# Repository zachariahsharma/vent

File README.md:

# Vynte Vent

KiCad hardware design for the Vynte smart vent, a battery-powered register for room-by-room HVAC comfort. The saved project revision is **v0.5.0**.

## Design files

- `Vent.kicad_pro`: open this project in KiCad.
- `Vent.kicad_sch` and `Vent.kicad_pcb`: main schematic and PCB layout.
- `3.3V-Buck-Boost.kicad_sch`, `5V-Boost.kicad_sch`, and `ExternalAutoprogramming.kicad_sch`: supporting schematic sheets.
- `production/`: saved fabrication archive, assembly CSV exports, IPC netlist, and stencil layers.
- `fabrication-toolkit-options.json`: saved fabrication export settings.

## Fabrication status

The production files are existing exports preserved with the project. The fabrication ZIP was generated on September 21, 2026; the PCB source was saved later, on September 22. These exports have not been verified against the latest source. Regenerate and review fabrication files, DRC, and ERC before ordering boards.

Local backups, analysis caches, and per-user KiCad settings are excluded from version control.

## Repository copies

Gitea is the development repository. The public GitHub copy includes the development history with credential files removed from every revision. Commit author and committer identities have been normalized to Zachariah K. Sharma at the repository owner's request; Gitea retains the original history.

No open-source license has been selected.

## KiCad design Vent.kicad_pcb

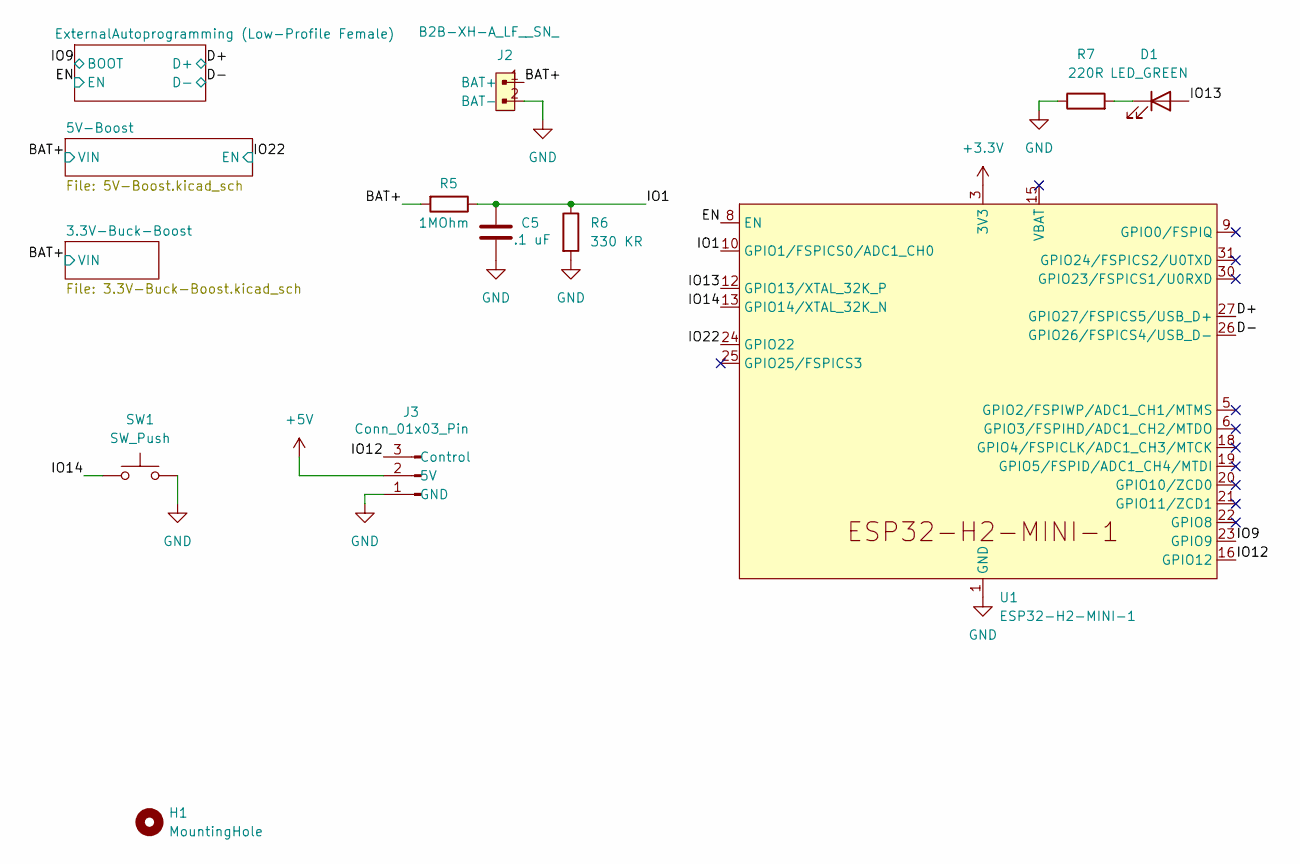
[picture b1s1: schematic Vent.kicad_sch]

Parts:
C5: .1 uF; C_0402_1005Metric; MPN C1005X7R1E104K050BB; Digi-Key_PN 445-7348-2-ND
D1: LED_GREEN; LED_D3.0mm_Horizontal_O1.27mm_Z2.0mm; MPN WP710A10GD; Digi-Key_PN 754-1603-ND
H1: MountingHole; MountingHole_2.2mm_M2
J2: B2B-XH-A_LF__SN_; SolderWire-0.5sqmm_1x02_P4.6mm_D0.9mm_OD2.1mm; MPN B2B-XH-A(LF)(SN); Digi-Key_PN 455-2247-ND
J3: Conn_01x03_Pin; SolderWire-0.25sqmm_1x03_P4.2mm_D0.65mm_OD1.7mm
R5: 1MOhm; R_0402_1005Metric; MPN RC0402FR-071ML; Digi-Key_PN 311-1.00MLRTR-ND
R6: 330 KR; R_0402_1005Metric; MPN RC0402FR-07330KL; Digi-Key_PN 311-330KLRTR-ND
R7: 220R; R_0402_1005Metric; MPN RC0402FR-07220RL; Digi-Key_PN 311-220LRTR-ND
SW1: SW_Push; SW_PUSH_6mm_H5mm; MPN PTS810SJK250SMTR LFS; Digi-Key_PN CKN10503TR-ND
U1: ESP32-H2-MINI-1; MPN ESP32-H2-MINI-1-H2S; Digi-Key_PN 1965-ESP32-H2-MINI-1-H2STR-ND

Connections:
+3.3V: U1.3 (3V3); also elsewhere on the board
+5V: J3.2 (5V); also elsewhere on the board
/BAT+: J2.1 (BAT+), R5.2; also elsewhere on the board
/D+: U1.27 (GPIO27/FSPICS5/USB_D+); also elsewhere on the board
/D-: U1.26 (GPIO26/FSPICS4/USB_D-); also elsewhere on the board
/EN: U1.8 (EN); also elsewhere on the board
/IO1: C5.1, R5.1, R6.1, U1.10 (GPIO1/FSPICS0/ADC1_CH0)
/IO9: U1.23 (GPIO9); also elsewhere on the board
/IO12: J3.3 (Control), U1.16 (GPIO12)
/IO13: D1.2 (A), U1.12 (GPIO13/XTAL_32K_P)
/IO14: SW1.1, U1.13 (GPIO14/XTAL_32K_N)
/IO22: U1.24 (GPIO22); also elsewhere on the board
GND: C5.2, J2.2 (BAT-), J3.1 (GND), R6.2, R7.1, SW1.2, U1.1 (GND), U1.2 (GND), U1.11 (GND), U1.14 (GND), U1.36 (GND), U1.37 (GND), U1.38 (GND), U1.39 (GND), U1.40 (GND), U1.41 (GND), U1.42 (GND), U1.43 (GND), U1.44 (GND), U1.45 (GND), U1.46 (GND), U1.47 (GND), U1.48 (GND), U1.49 (GND), U1.50 (GND), U1.51 (GND), U1.52 (GND), U1.53 (GND); also elsewhere on the board
unnamed: D1.1 (K), R7.2

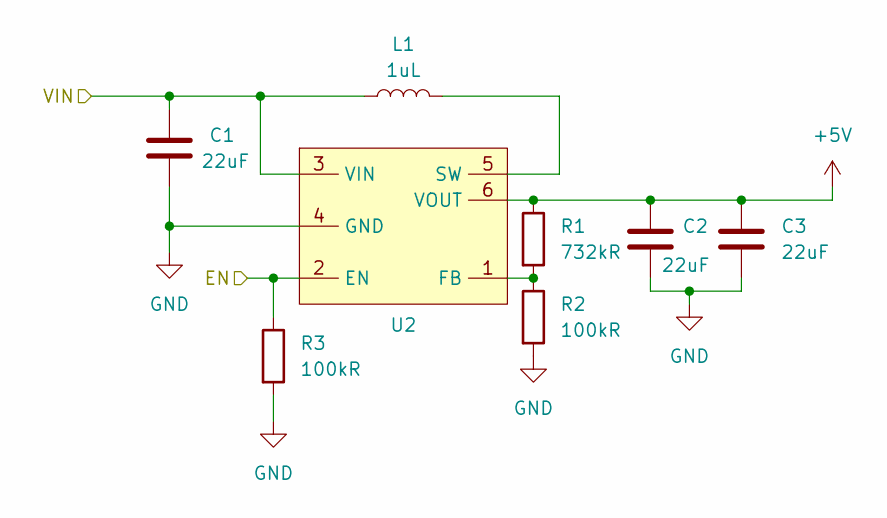
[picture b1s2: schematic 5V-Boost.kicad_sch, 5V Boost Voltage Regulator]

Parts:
C1, C2, C3: 22uF; C_1206_3216Metric; MPN TMK316BBJ226ML-T; Digi-Key_PN 587-3246-1-ND
L1: 1uL; L_Wuerth_MAPI-4030; MPN 74438357010; Digi-Key_PN 732-11197-1-ND
R1: 732kR; R_0603_1608Metric; MPN ERJ-3EKF7323V; Digi-Key_PN P732KHCT-ND
R2, R3: 100kR; R_0603_1608Metric; MPN RC0603FR-07100KL; Digi-Key_PN 311-100KHRCT-ND
U2: SOT-563; MPN TPS61023DRLR; Digi-Key_PN 296-TPS61023DRLRCT-ND

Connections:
+5V: C2.1, C3.1, R1.1, U2.6 (VOUT); also elsewhere on the board
/BAT+: C1.1, L1.1, U2.3 (VIN); also elsewhere on the board
/IO22: R3.1, U2.2 (EN); also elsewhere on the board
GND: C1.2, C2.2, C3.2, R2.2, R3.2, U2.4 (GND); also elsewhere on the board
unnamed: R1.2, R2.1, U2.1 (FB)
unnamed: L1.2, U2.5 (SW)

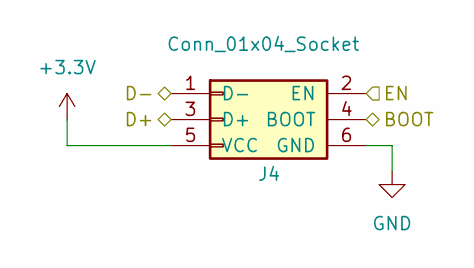
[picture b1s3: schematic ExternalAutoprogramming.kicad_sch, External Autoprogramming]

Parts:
J4: Conn_01x04_Socket; Tag-Connect_TC2030-IDC-NL_2x03_P1.27mm_Vertical; MPN TC2030-IDC-NL

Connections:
+3.3V: J4.5 (VCC); also elsewhere on the board
/D+: J4.3 (D+); also elsewhere on the board
/D-: J4.1 (D-); also elsewhere on the board
/EN: J4.2 (EN); also elsewhere on the board
/IO9: J4.4 (BOOT); also elsewhere on the board
GND: J4.6 (GND); also elsewhere on the board

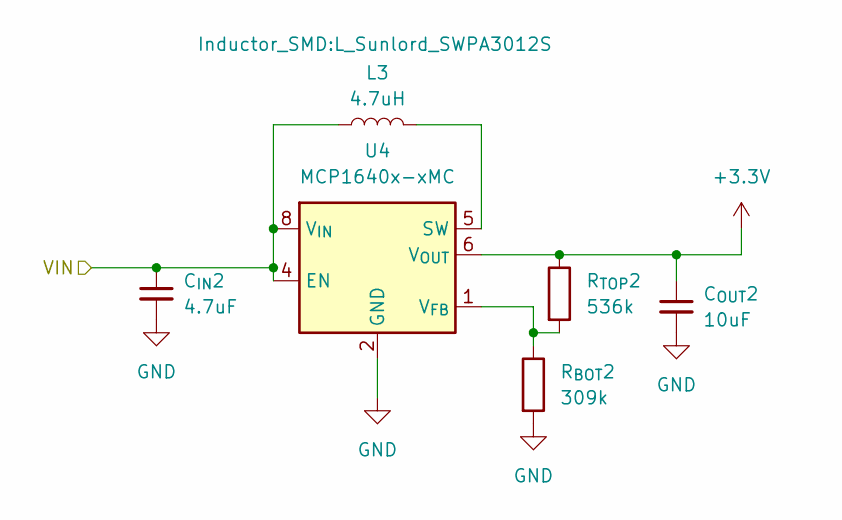
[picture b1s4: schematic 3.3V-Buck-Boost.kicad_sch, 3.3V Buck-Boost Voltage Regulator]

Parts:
C_{IN}2: 4.7uF; C_0805_2012Metric; MPN CL21A475KAQNNNE; Digi-Key_PN 1276-1244-2-ND
C_{OUT}2: 10uF; C_0805_2012Metric; MPN TMK212BBJ106KGHT; Digi-Key_PN 587-4334-2-ND
L3: 4.7uH; L_Sunlord_SWPA3012S; MPN SWPA3012S4R7MT; Digi-Key_PN 3442-SWPA3012S4R7MTTR-ND
R_{BOT}2: 309k; R_0603_1608Metric; MPN RC0603FR-07309KL; Digi-Key_PN 311-309KHRTR-ND
R_{TOP}2: 536k; R_0603_1608Metric; MPN RC0603FR-07536KL; Digi-Key_PN 311-536KHRTR-ND
U4: MCP1640x-xMC; DFN-8-1EP_3x2mm_P0.5mm_EP1.75x1.45mm; MPN MCP1640T-I/MC; Digi-Key_PN MCP1640T-I/MCTR-ND

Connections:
+3.3V: C_{OUT}2.1, R_{TOP}2.1, U4.6 (V_{OUT}), U4.7 (V_{OUT}); also elsewhere on the board
/BAT+: C_{IN}2.1, L3.1, U4.4 (EN), U4.8 (V_{IN}); also elsewhere on the board
GND: C_{IN}2.2, C_{OUT}2.2, R_{BOT}2.2, U4.2 (GND), U4.3 (GND), U4.9 (GND); also elsewhere on the board
unnamed: L3.2, U4.5 (SW)
unnamed: R_{BOT}2.1, R_{TOP}2.2, U4.1 (V_{FB})

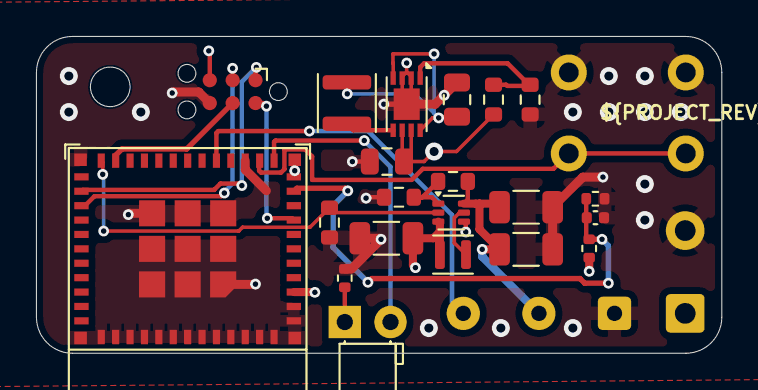
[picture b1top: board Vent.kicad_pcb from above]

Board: 4 copper layers, 38.1 x 17.6 mm, 25 parts (1 on the bottom side), 18 nets.

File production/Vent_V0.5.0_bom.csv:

Designator,Footprint,Quantity,Value,LCSC Part #
"C1, C2, C3",1206,3,22uF,CL31A226KAHNNNE
C5,0402,1,.1 uF,C1005X7R1E104K050BB
C_{IN}2,0805,1,4.7uF,CL21A475KAQNNNE
C_{OUT}2,0805,1,10uF,TMK212BBJ106KGHT
D1,LED_D3.0mm_Horizontal_O1.27mm_Z2.0mm,1,LED_GREEN,WP710A10GD
J2,SolderWire-0.5sqmm_1x02_P4.6mm_D0.9mm_OD2.1mm,1,B2B-XH-A_LF__SN_,B2B-XH-A(LF)(SN)
J3,SolderWire-0.25sqmm_1x03_P4.2mm_D0.65mm_OD1.7mm,1,Conn_01x03_Pin,
J4,Tag-Connect_TC2030-IDC-NL_2x03_P1.27mm_Vertical,1,Conn_01x04_Socket,
L1,L_Murata_DFE201610P,1,1uL,DFE201612E-1R0M=P2
L3,L_Sunlord_SWPA3012S,1,4.7uH,SWPA3012S4R7MT
R1,0603,1,732kR,RC0603FR-07732KL
"R2, R3",0603,2,100kR,RC0603FR-07100KL
R5,0402,1,1MOhm,RC0402FR-071ML
R6,0402,1,330 KR,RC0402FR-07330KL
R7,0402,1,220R,RC0402FR-07220RL
R_{BOT}2,0603,1,309k,RC0603FR-07309KL
R_{TOP}2,0603,1,536k,RC0603FR-07536KL
SW1,SW_PUSH_6mm_H5mm,1,SW_Push,PTS810SJK250SMTR LFS
U1,ESP32-H2-MINI-1,1,ESP32-H2-MINI-1,ESP32-H2-MINI-1-H2S
U2,SOT-563,1,~,TPS61023DRLR
U4,DFN-8-1EP_3x2mm_P0.5mm_EP1.75x1.45mm,1,MCP1640x-xMC,MCP1640T-I/MC

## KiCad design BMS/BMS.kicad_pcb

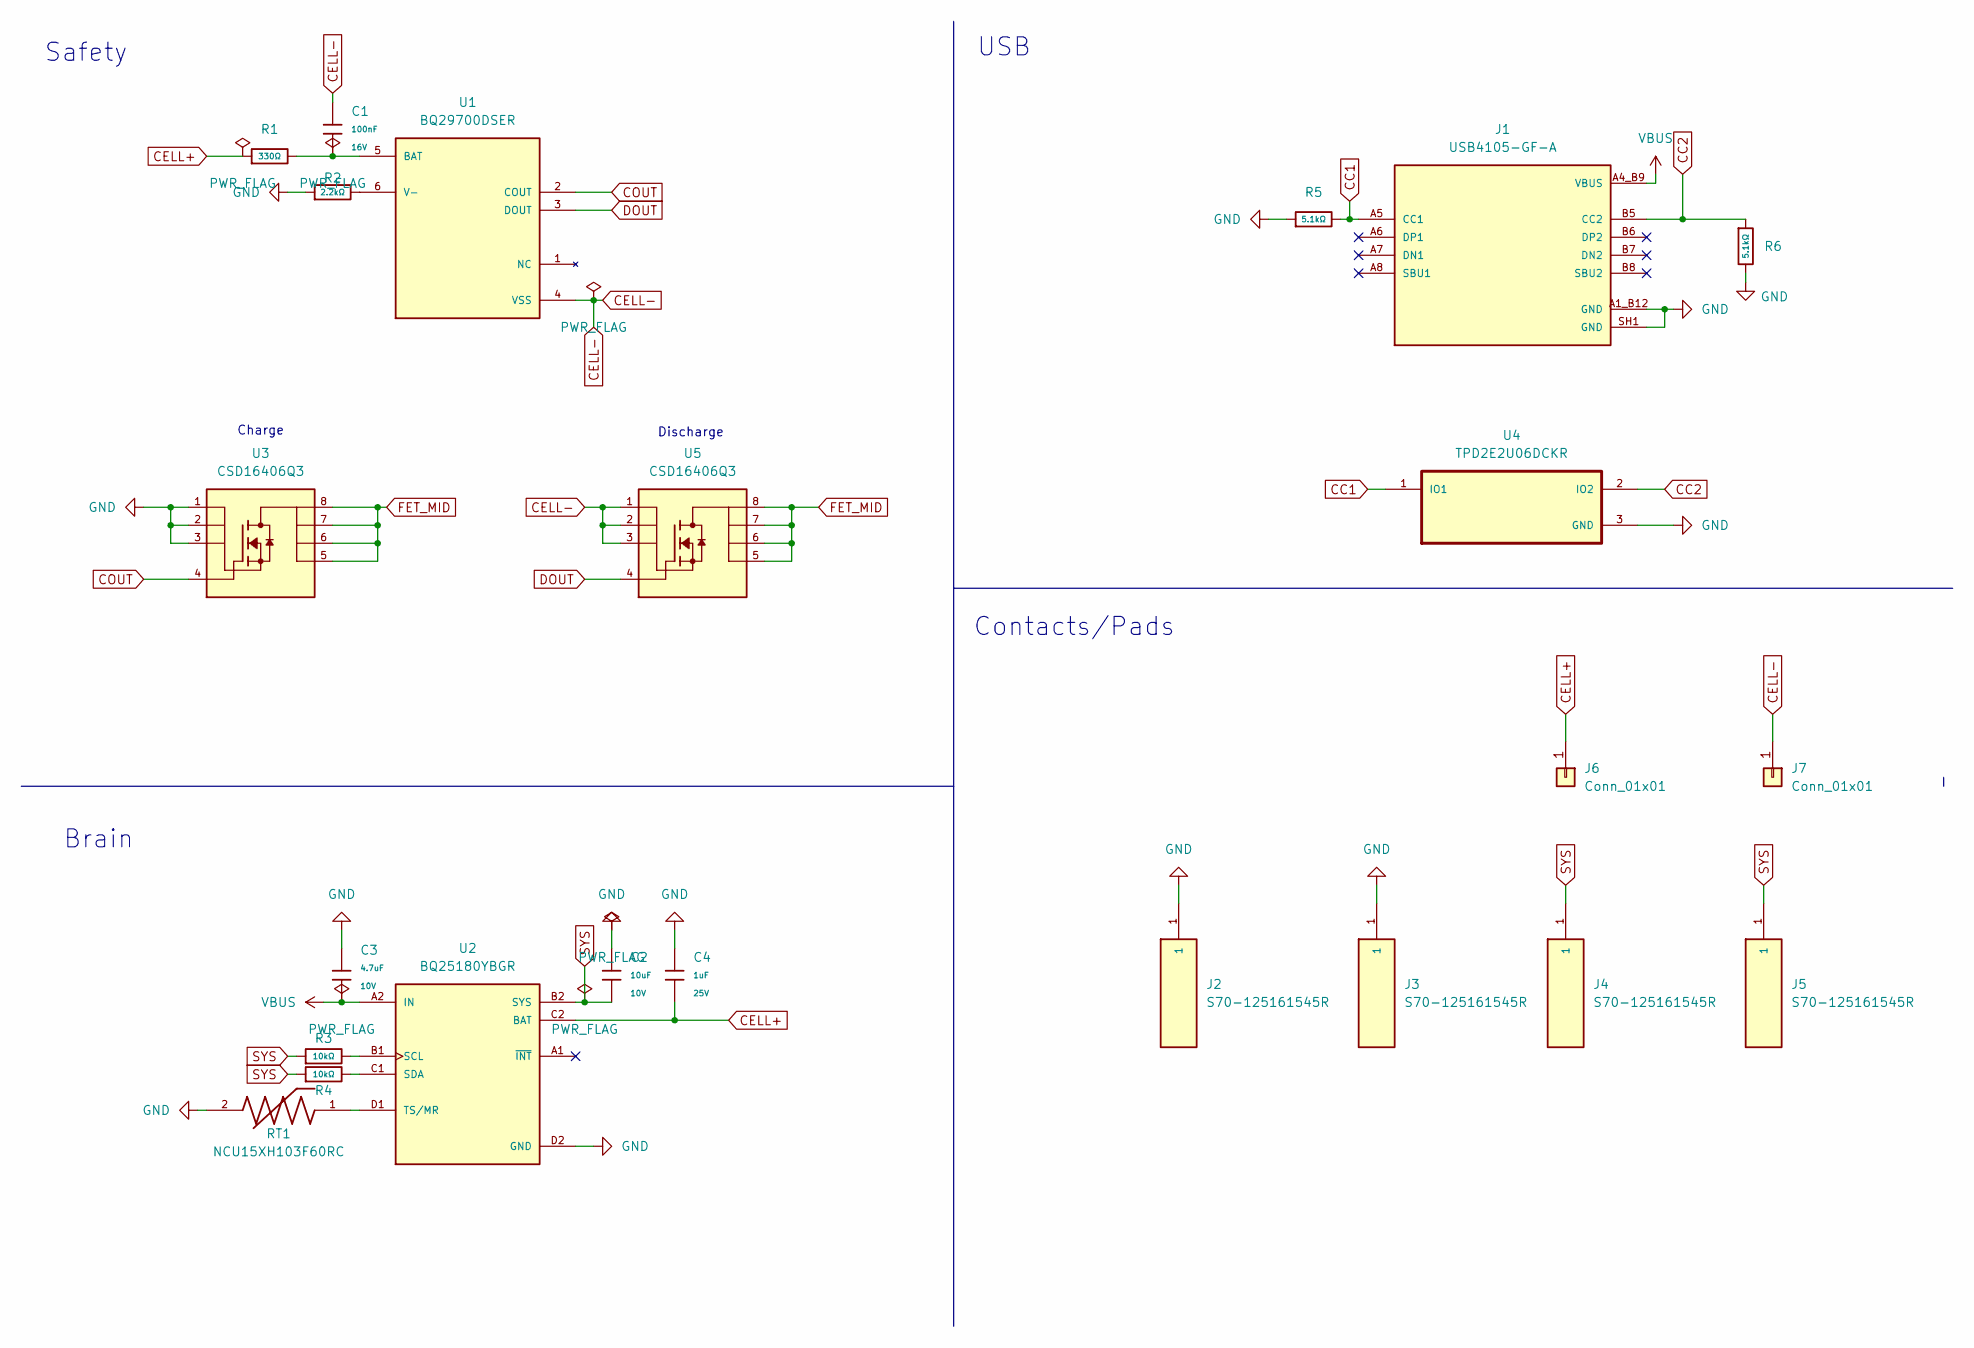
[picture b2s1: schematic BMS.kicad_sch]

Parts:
C1: 100nF; C_0402; Voltage Rated 16V; Tolerance ±10%; Part CL05B104KO5NNNC; LCSC C1525
C2: 10uF; C_0603; Voltage Rated 10V; Tolerance ±10%; Part CL10A106KP8NNNC; LCSC C19702
C3: 4.7uF; C_0402; Voltage Rated 10V; Tolerance ±20%; Part CL05A475MP5NRNC; LCSC C23733
C4: 1uF; C_0402; Voltage Rated 25V; Tolerance ±10%; Part CL05A105KA5NQNC; LCSC C52923
J1: USB4105-GF-A; GCT_USB4105-GF-A; PARTREV B4
J2, J3, J4, J5: S70-125161545R; ENIG_PAD; PARTREV 6
J6, J7: Conn_01x01; MountingHole_2.2mm_M2_DIN965_Pad
R1: 330Ω; R_0402; Overload Voltage (Max) 50V; Tolerance ±1%; Part 0402WGF3300TCE; LCSC C25104
R2: 2.2kΩ; R_0402; Overload Voltage (Max) 50V; Tolerance ±1%; Part 0402WGF2201TCE; LCSC C25879
R3, R4: 10kΩ; R_0402; Overload Voltage (Max) 50V; Tolerance ±1%; Part 0402WGF1002TCE; LCSC C25744
R5, R6: 5.1kΩ; R_0402; Overload Voltage (Max) 50V; Tolerance ±1%; Part 0402WGF5101TCE; LCSC C25905
RT1: NCU15XH103F60RC; THRMC1005X55N
U1: BQ29700DSER; SON50P150X150X80-6N; PARTREV G
U2: BQ25180YBGR; IC_BQ25180YBGR; PARTREV C
U3, U5: CSD16406Q3; TRANS_CSD16406Q3
U4: TPD2E2U06DCKR; SOT65P210X110-3N; PARTREV C

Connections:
CC1: J1.A5 (CC1), R5.2, U4.1 (IO1)
CC2: J1.B5 (CC2), R6.1, U4.2 (IO2)
CELL+: C4.2, J6.1, R1.1, U2.C2 (BAT)
CELL-: C1.1, J7.1, U1.4 (VSS), U5.1, U5.2, U5.3
COUT: U1.2 (COUT), U3.4
DOUT: U1.3 (DOUT), U5.4
FET_MID: U3.5, U3.6, U3.7, U3.8, U5.5, U5.6, U5.7, U5.8
GND: C2.2, C3.1, C4.1, J1.A1_B12 (GND), J1.B1_A12 (GND), J1.SH1 (SHELL_GND), J1.SH2 (SHELL_GND), J1.SH3 (SHELL_GND), J1.SH4 (SHELL_GND), J2.1, J3.1, R2.1, R5.1, R6.2, RT1.2, U2.D2 (GND), U3.1, U3.2, U3.3, U4.3 (GND)
unnamed: C1.2, R1.2, U1.5 (BAT)
unnamed: R2.2, U1.6 (V-)
unnamed: R3.2, U2.B1 (SCL)
unnamed: R4.2, U2.C1 (SDA)
unnamed: RT1.1, U2.D1 (TS/MR)
SYS: C2.1, J4.1, J5.1, R3.1, R4.1, U2.B2 (SYS)
VBUS: C3.2, J1.A4_B9 (VBUS), J1.B4_A9 (VBUS), U2.A2 (IN)

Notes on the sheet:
Charge
Safety
USB
Discharge
Contacts/Pads
Brain

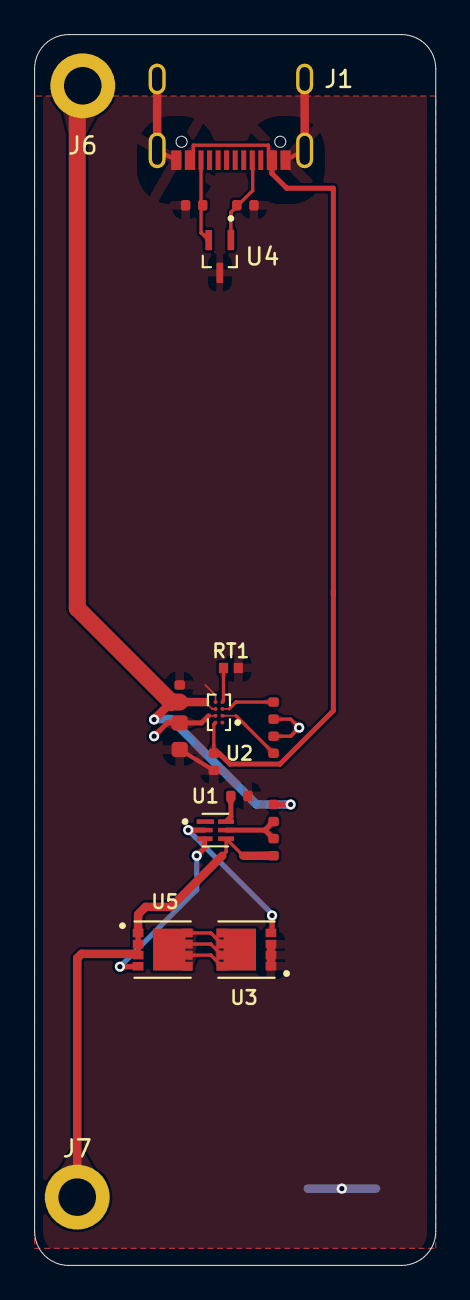
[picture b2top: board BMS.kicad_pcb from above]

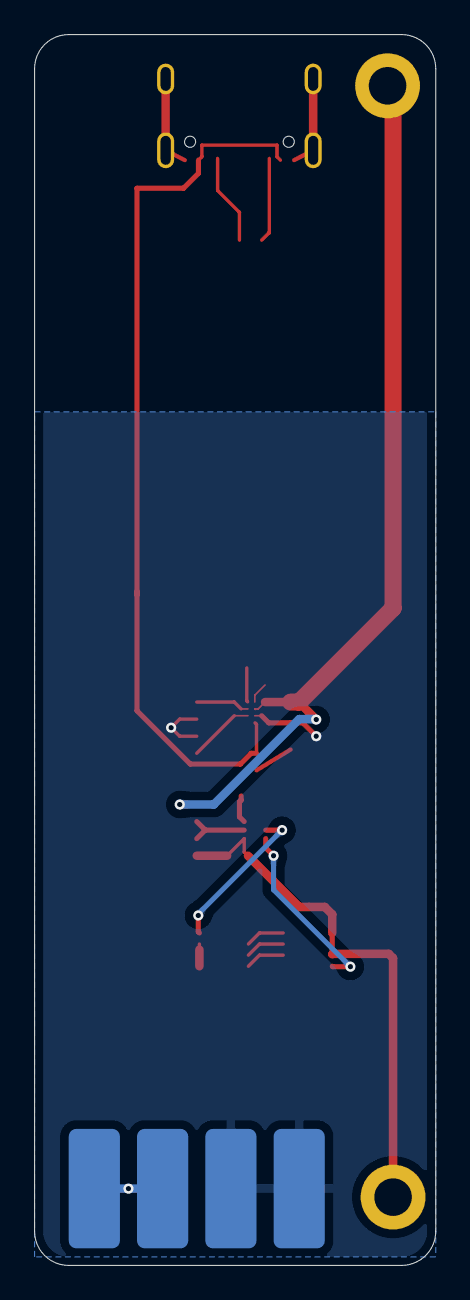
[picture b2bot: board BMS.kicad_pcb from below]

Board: 2 copper layers, 23.5 x 72.1 mm, 23 parts (4 on the bottom side), 15 nets.

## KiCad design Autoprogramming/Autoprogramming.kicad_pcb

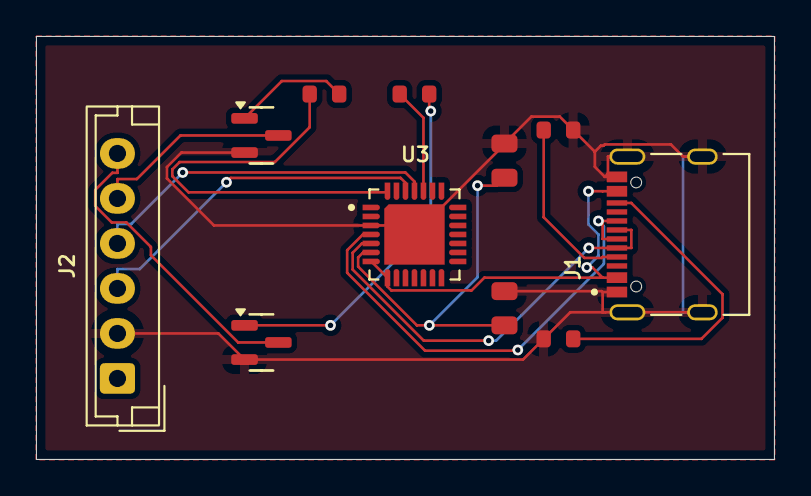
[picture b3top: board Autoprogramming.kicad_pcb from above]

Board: 2 copper layers, 41.0 x 23.5 mm, 11 parts (0 on the bottom side), 15 nets.

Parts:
C1: 100nF; C_0805_100nF
C2: 4.7uF; C_0805_4u7
J1: TYPE-C-31-M-12; HRO_TYPE-C-31-M-12
J2: Conn_01x06_Pin; JST_EH_B6B-EH-A_1x06_P2.50mm_Vertical
Q1, Q2: S8050 J3Y 200-350; Q_SOT-23
R3, R4: 5.1kΩ; R_0603
R5, R6: 10kΩ; R_0603
U3: CP2102N-A02-GQFN28R; IC_CP2102N-A02-GQFN28R

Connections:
DTR: R6.1, U3.28
EN: J2.5, Q1.3 (C)
GND: C1.2, C2.2, J1.A1_B12, J1.B1_A12, J1.S1, J1.S2, J1.S3, J1.S4, J2.2, Q1.2 (E), Q2.2 (E), R3.2, R4.1, U3.3, U3.29
IO0: J2.6, Q2.3 (C)
unnamed: J1.A5, R3.1
unnamed: J1.B5, R4.2
unnamed: Q1.1 (B), R6.2
unnamed: Q2.1 (B), R5.2
unnamed: C1.1, C2.1, U3.6
RTS: R5.1, U3.24
RXD0: J2.3, U3.26
TXD0: J2.4, U3.25
USB_D+: J1.A6, J1.B6, U3.4
USB_D-: J1.A7, J1.B7, U3.5
VBUS: J1.A4_B9, J1.B4_A9, U3.7, U3.8

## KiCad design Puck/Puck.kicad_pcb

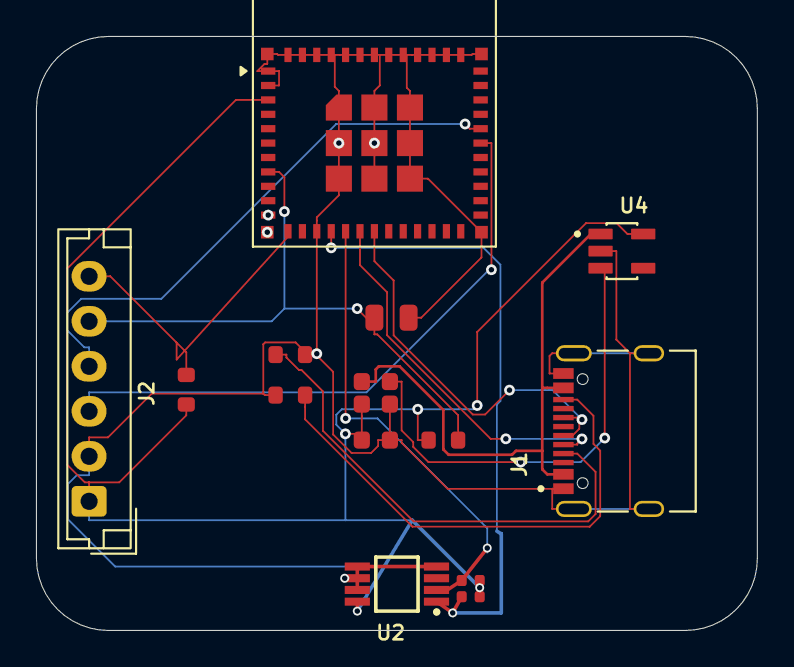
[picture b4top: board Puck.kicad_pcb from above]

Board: 2 copper layers, 40.1 x 33.0 mm, 15 parts (0 on the bottom side), 14 nets.

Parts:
C3, C4: 10uF; C_0603
C5: 1uF; C_0603
C6: 100nF; C_0805
J1: TYPE-C-31-M-12; HRO_TYPE-C-31-M-12
J2: AUTO_PROG_UART; JST_EH_B6B-EH-A_1x06_P2.50mm_Vertical
R1, R2: 4.7kΩ; R_0402
R3, R4: 5.1kΩ; R_0603
R7, R8: 10kΩ; R_0603
U1: ESP32-C6-MINI-1-H4; ESP32-C6-MINI-1
U2: MCP9808T-E_MS; SOP65P490X110-8N
U4: AP2112K-3.3TRG1; SOT95P285X140-5N

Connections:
+3.3V: C4.1, C5.1, J2.1, R1.2, R2.2, R7.1, R8.1, U1.3, U2.8 (VDD), U4.5 (VOUT)
EN: C6.1, J2.5, R7.2, U1.8
GND: C4.2, C5.2, C6.2, J1.A1_B12 (GND), J1.B1_A12 (GND), J1.S1 (SHIELD), J1.S2 (SHIELD), J1.S3 (SHIELD), J1.S4 (SHIELD), J2.2, R3.2, R4.1, U1.1, U1.2, U1.11, U1.14, U1.36, U1.37, U1.38, U1.39, U1.40, U1.41, U1.42, U1.43, U1.44, U1.45, U1.46, U1.47, U1.48, U1.49, U1.50, U1.51, U1.52, U1.53, U2.4 (GND), U2.5 (A2), U2.6 (A1), U2.7 (A0), U4.2 (GND)
I2C_SCL: R2.1, U1.16, U2.2 (SCL)
I2C_SDA: R1.1, U1.15, U2.1 (SDA)
IO0: J2.6, R8.2, U1.12
unnamed: J1.A5 (CC1), R3.1
unnamed: J1.B5 (CC2), R4.2
unnamed: C3.2, U4.3 (EN)
RXD0: J2.3, U1.30
TXD0: J2.4, U1.31
USB_D+: J1.A6 (DP1), J1.B6 (DP2), U1.18
USB_D-: J1.A7 (DN1), J1.B7 (DN2), U1.17
VBUS: C3.1, J1.A4_B9 (VBUS), J1.B4_A9 (VBUS), U4.1 (VIN)

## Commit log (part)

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2026-01-22 Added a dockerfile temporarily removed media in order for first pitch (kinda sloppy)
2026-01-22 fixed dockerifle mb
2026-01-22 linting
2026-01-22 no frozne lockfile
2026-01-22 mobile friendly
2026-01-23 temperature not cold-air
2026-01-23 no reviews
2026-02-18 chore: update website
2026-02-18 credentials
2026-04-08 Redesign homepage and add product renders
2026-04-08 infra: Move website code into website folder
2026-04-08 Autoprogramming Circuit
2026-04-08 Started taking a look a PCB Layout
2026-04-08 USB-to-UART
2026-04-08 Added symbols, models, footprints for BMS and added wiring for Safety and the Brain
2026-04-08 Fixed most of the bugs hopefully
2026-04-08 Added placeholders for the other PCB's
2026-04-08 Reorganized Files
2026-04-08 Finished wiring for Brain, changed to 4 leafs without EN because we're using 1S4P config
2026-04-08 infra: Move electronics into electronics folder
2026-04-08 infra: Move dot files to website
2026-04-08 infra: Move mobile source code to mobile folder
2026-04-08 infra: Bring back website .gitignore
2026-04-08 infra: Move mobile .gitignore back to mobile folder
2026-04-09 adjusted the pcb
2026-04-09 Worked out the PCB Layout for the BMS, now I just need to size traces
2026-04-09 Traces seem decent, just working out some DRC problems
2026-04-10 Finalized Everything for Review, exported gerbers
2026-05-09 Autoprogramming, Finish off BMS, Add comps to Vent, and do a bunch of mobile stuff
2026-05-25 infra: Remove everything but electronics
2026-05-25 infra: Remove redundant .gitignores
2026-06-10 Puck: shrink board 56.8mm→43mm, close sensor dead zone
    Move MCP9808T temp sensor (U2) and I2C pull-ups (R1, R2) up 17mm.
    Tighten C4/C5/R7 passive cluster. Resize board outline.
    FreeRouting v2.2.4 re-routes from scratch; DRC: 0 violations.
2026-06-10 Vent: clear all traces, reposition J3/J4/U1, FreeRouting re-route; DRC: 0 errors
    Component fixes required due to out-of-bounds pads from prior task placement:
    - U1 (ESP32-H2): shift down 0.165mm so top pads are 0.5mm from board edge
    - J3 (boost header): rotate 90° and move to (45,25) to clear U1/L1/J1/J4 courtyards
    - J4 (BMS spring contacts): move to x=52.85 so pad-4 right edge is 0.15mm from board edge
    - Zone outlines trimmed to 0.5mm inside board edge for clean GND pour fill
    DRC rule adjustments for 55×15.97mm compact form factor:
2026-06-10 Vent: fix +3V3 connectivity to R1 pad 1 via B.Cu via; refill GND zones
    Add B.Cu via at R1 pad 1 (12.675, 13.2) with B.Cu trace to the existing
    +3V3 B.Cu network at (15.45, 13.2)→(15.45, 18.192), restoring connectivity
    that was missed by FreeRouting in Task 9.
    DRC result: 0 rule violations (9 silkscreen warnings, unchanged from Task 9),
    7 unconnected items (improved from 8):
    - GND: zone fill fragmentation around 5 isolated pads (pre-existing,
2026-06-10 Vent: move J4 spring contacts to bottom edge, reduce DRC
    - Relocated J4 castellation spring contacts to bottom board edge
    (mechanical requirement: contacts must protrude at very bottom)
    - Re-routed affected nets via FreeRouting baseline
    - Removed 3 GND F.Cu segments near U1 pad 25 (zone fill covers GND)
    - Added Vent.kicad_dru custom rules to exempt U1 NC castellation pads
    from clearance/hole_clearance checks (mechanical pads, no electrical net)
2026-06-10 Vent: widen +5V_SERVO orthogonal segments to 0.30mm
    Two non-diagonal +5V_SERVO segments widened to 0.30mm at the
    connector stubs (J1 area). The diagonal segment is kept at 0.20mm
    because widening it triggers clearance violations against the
    BB_SW1 via at (49.345, 19.310).
    Full widening of BB_SW1/SW2 and BMS_SYS_CONTACT is blocked by
    buck-converter (U2/L1) layout density — those nets need manual
2026-06-10 docs: document pending schematic revisions and routing
    Records the medium-priority datasheet findings as engineering punch
    lists in BUILD_NOTES.md for both boards. These require manual KiCad
    GUI application because scripted .kicad_sch edits have repeatedly
    corrupted the schematic.
    Pending revisions:
    - Vent: 10kΩ pull-down on SERVO_BOOST_EN (IO25 strapping reliability)
2026-06-10 docs: note schematic re-layout requires manual KiCad GUI work
    Records that automated/scripted schematic re-layout attempts failed
    (the second attempt corrupted Vent.kicad_sch). Manual GUI work is
    the proper next step. Includes target grouping for both boards.
2026-06-10 Vent: route SERVO_PWM via west of GND wall, 0 routing-electrical DRC
    Previous Plan G connected SERVO_PWM but its F.Cu south leg at x=47 crossed
    BB_SW1 diagonal/horizontal and was too close to BMS_SYS_CONTACT diagonal,
    yielding 4 routing violations.
    New topology: via-on-pad at U1.24 -> B.Cu east-south to (46.7, 15) (stays
    west of GND B.Cu vertical wall at x=47.344) -> south to (46.7, 19.8) ->
    via to F.Cu in clean band between BB_SW1 horizontal (y=19.31) and J1.3
2026-06-10 Vent: widen BB_SW1/SW2/BMS_SYS_CONTACT to 0.25mm with buck DRU rule
    Aggressive widening (BB_SW=0.30, BMS=0.40) was geometrically infeasible —
    collisions of 0.085-0.18mm against U2 GND pads and adjacent switch nets.
    Conservative widening (0.25mm uniform for buck nets, +5V_SERVO orthogonal
    0.30mm, +5V_SERVO diagonal kept 0.20mm to preserve BB_SW1 via clearance)
    fits within a new DRU rule allowing 0.15mm clearance among the three
    buck-internal nets and their U2/L1 footprint pads.
2026-06-10 Puck: stitch B.Cu GND zone to F.Cu network with 5 vias
    The B.Cu GND pour was electrically isolated from the F.Cu GND chain
    and from two GND pads on U1 (pins 11 and 52). Added stitching vias
    at (140.05, 92.20), (137.35, 84.50), (137.30, 85.45), (141.275, 80.50)
    and (143.250, 80.50) to bridge the zones into one GND net.
    DRC now reports 0 violations and 1 remaining unconnected item:
    USB_D- A7 <-> B7 on J1. That tie cannot be routed under the board's
2026-06-10 docs: mark layout optimization spec as implemented; record as-built dims
    Puck 40.10x43.05mm, Vent 55.05x16.02mm. Puck has 1 documented
    unconnected (USB_D- A7<->B7) requiring GUI fix; Vent has 0 errors,
    0 unconnected, 10 cosmetic silk warnings. Remaining schematic edits
    and re-layouts noted as KiCad GUI work in the BUILD_NOTES files.
2026-06-10 docs: track Puck/Vent layout optimization implementation plan
    The plan that produced the as-built Puck 40x43mm and Vent 55x16mm
    boards. Kept for reference alongside the spec.
2026-06-11 Optimized the sizes of the PCB's
2026-06-11 Puck: convert to single-sided assembly (R1/R2/U2 -> F.Cu)
    Flip R1, R2, U2 from B.Cu to F.Cu so all 15 components populate one side
    (single reflow pass); board stays 2-layer copper. Re-route the sensor
    pocket: GND links + via to B.Cu pour, I2C escapes to trunks, and +3.3V's
    U2 leg on B.Cu (bottom F.Cu channel too narrow under the SDA via per the
    0.5mm edge clearance). DRC: 0 violations, 1 documented USB_D- unconnected.
